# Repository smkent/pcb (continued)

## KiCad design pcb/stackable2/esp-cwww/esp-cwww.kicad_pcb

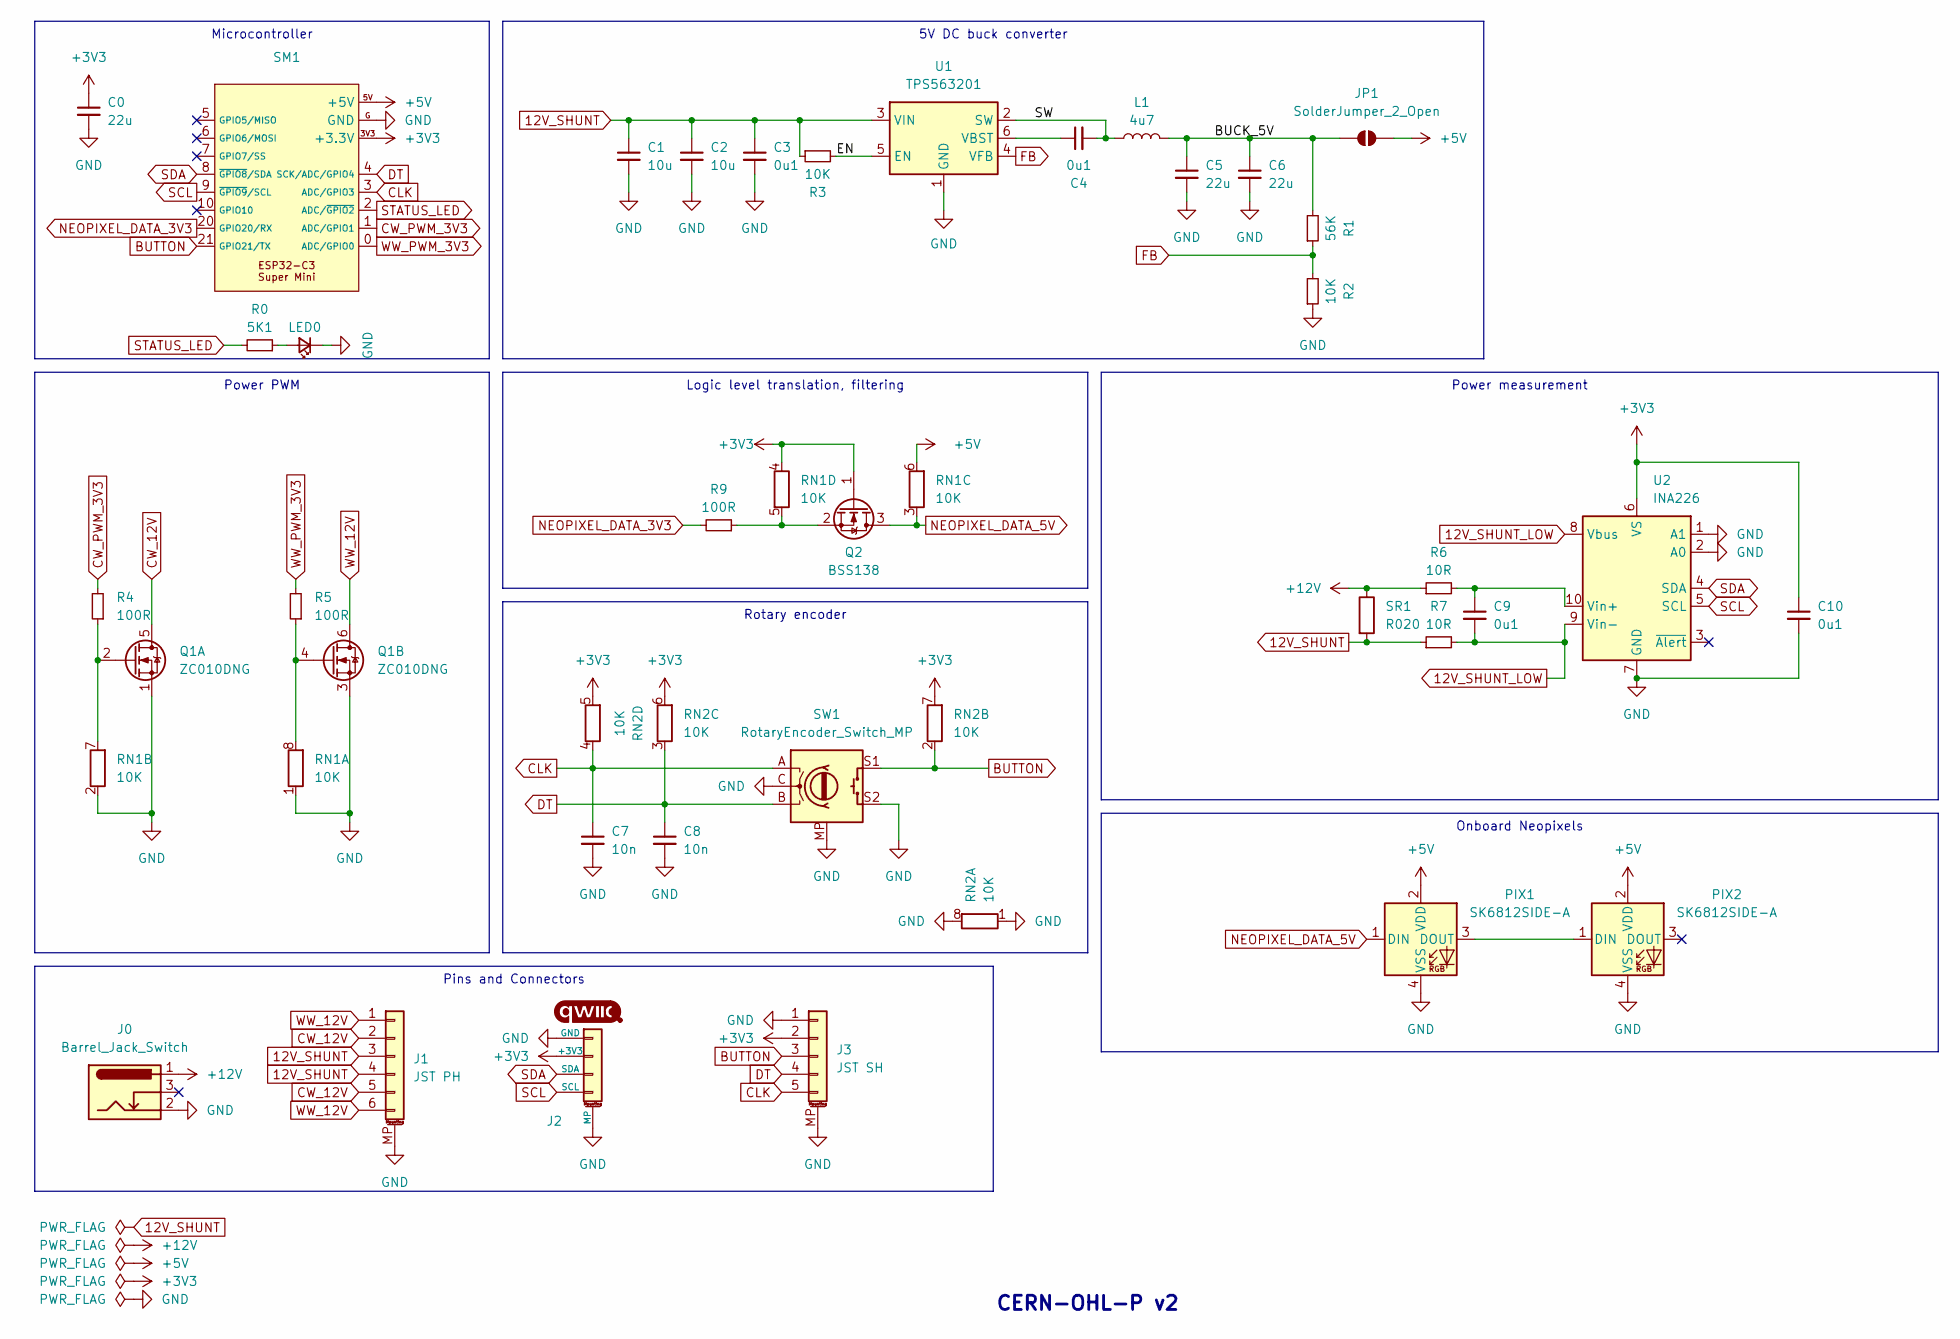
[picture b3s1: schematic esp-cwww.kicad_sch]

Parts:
C0, C5, C6: 22u; C_0603_1608Metric_Pad1.08x0.95mm_HandSolder
C1, C2: 10u; C_0603_1608Metric_Pad1.08x0.95mm_HandSolder
C3, C4: 0u1; C_0603_1608Metric_Pad1.08x0.95mm_HandSolder
C7, C8: 10n; C_0603_1608Metric_Pad1.08x0.95mm_HandSolder
C9, C10: 0u1; C_0402_1005Metric; LCSC Part C152814
J0: Barrel_Jack_Switch; BarrelJack_DC-050_SMT_Horizontal
J1: JST PH; JST_PH_S6B-PH-SM4-TB_1x06-1MP_P2.00mm_Horizontal
J2: Qwiic; Qwiic-SMD-horizontal-logo
J3: JST SH; JST_SH_SM05B-SRSS-TB_1x05-1MP_P1.00mm_Horizontal
JP1: SolderJumper_2_Open; SolderJumper-2_P1.3mm_Open_TrianglePad1.0x1.5mm
L1: 4u7; L_1008_2520Metric
LED0: LED_Small; LED_0603_1608Metric_Pad1.05x0.95mm_HandSolder_simple
PIX1, PIX2: SK6812SIDE-A; LED_SK6812SIDE-A_4.0x1.6mm; LCSC Part C2890037
Q1: ZC010DNG; PDFN-8_L3.2-W3.1-P0.65-LS3.4-BL-EP2; LCSC Part C36499170
Q2: BSS138; SOT-23
R0: 5K1; R_0402_1005Metric
R1: 56K; R_0603_1608Metric_Pad0.98x0.95mm_HandSolder
R2, R3: 10K; R_0603_1608Metric_Pad0.98x0.95mm_HandSolder
R4, R5, R9: 100R; R_0603_1608Metric_Pad0.98x0.95mm_HandSolder
R6, R7: 10R; R_0402_1005Metric; LCSC Part C25077
RN1, RN2: 10K; R_Array_Convex_4x0603
SM1: ESP32-C3-Super-Mini-Castellated-SMD-only
SR1: R020; R_2512_6332Metric_Pad1.40x3.35mm_HandSolder; LCSC Part C5375467
SW1: RotaryEncoder_Switch_MP; RotaryEncoder_Alps_EC11-Switch_Combo_H20mm
U1: TPS563201; SOT-23-6
U2: INA226; VSSOP-10_3x3mm_P0.5mm

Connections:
12V_SHUNT: C1.1, C2.1, C3.1, J1.3, J1.4, R3.1, R7.1, SR1.2, U1.3 (VIN)
12V_SHUNT_LOW: C9.2, R7.2, U2.8 (Vbus), U2.9 (Vin-)
+3V3: C0.1, C10.1, J2.2 (+3V3), J3.2, Q2.1 (G), RN1.4 (R4.1), RN2.5 (R4.2), RN2.6 (R3.2), RN2.7 (R2.2), SM1.3V3 (+3.3V), U2.6 (VS)
+5V: JP1.2 (B), PIX1.2 (VDD), PIX2.2 (VDD), RN1.6 (R3.2), SM1.5V (+5V)
+12V: J0.1, R6.1, SR1.1
/BUCK_5V: C5.1, C6.1, JP1.1 (A), L1.2, R1.2
/EN: R3.2, U1.5 (EN)
/SW: C4.2, L1.1, U1.2 (SW)
BUTTON: J3.3, RN2.2 (R2.1), SM1.21 (GPIO21/TX), SW1.S1
CLK: C7.1, J3.5, RN2.4 (R4.1), SM1.3 (ADC/GPIO3), SW1.A
CW_12V: J1.2, J1.5, Q1.5 (D)
CW_PWM_3V3: R4.2, SM1.1 (ADC/GPIO1)
DT: C8.1, J3.4, RN2.3 (R3.1), SM1.4 (SCK/ADC/GPIO4), SW1.B
FB: R1.1, R2.2, U1.4 (VFB)
GND: C0.2, C1.2, C2.2, C3.2, C5.2, C6.2, C7.2, C8.2, C10.2, J0.2, J1.MP (MountPin), J2.1 (GND), J2.MP, J3.1, J3.MP (MountPin), LED0.1 (K), PIX1.4 (VSS), PIX2.4 (VSS), Q1.1 (S), Q1.3 (S), R2.1, RN1.1 (R1.1), RN1.2 (R2.1), RN2.1 (R1.1), RN2.8 (R1.2), SM1.G (GND), SW1.C, SW1.MP, SW1.S2, U1.1 (GND), U2.1 (A1), U2.2 (A0), U2.7 (GND)
NEOPIXEL_DATA_3V3: R9.2, SM1.20 (GPIO20/RX)
NEOPIXEL_DATA_5V: PIX1.1 (DIN), Q2.3 (D), RN1.3 (R3.1)
unnamed: LED0.2 (A), R0.1
unnamed: PIX1.3 (DOUT), PIX2.1 (DIN)
unnamed: Q1.2 (G), R4.1, RN1.7 (R2.2)
unnamed: Q1.4 (G), R5.1, RN1.8 (R1.2)
unnamed: Q2.2 (S), R9.1, RN1.5 (R4.2)
unnamed: C4.1, U1.6 (VBST)
unnamed: C9.1, R6.2, U2.10 (Vin+)
SCL: J2.4 (SCL), SM1.9 (~GPIO9/SCL), U2.5 (SCL)
SDA: J2.3 (SDA), SM1.8 (~GPIO8/SDA), U2.4 (SDA)
STATUS_LED: R0.2, SM1.2 (ADC/~GPIO2)
WW_12V: J1.1, J1.6, Q1.6 (D)
WW_PWM_3V3: R5.2, SM1.0 (ADC/GPIO0)

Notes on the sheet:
Rotary encoder
5V DC buck converter
Onboard Neopixels
Logic level translation, filtering
Power PWM
Power measurement
Pins and Connectors
Microcontroller
CERN-OHL-P v2

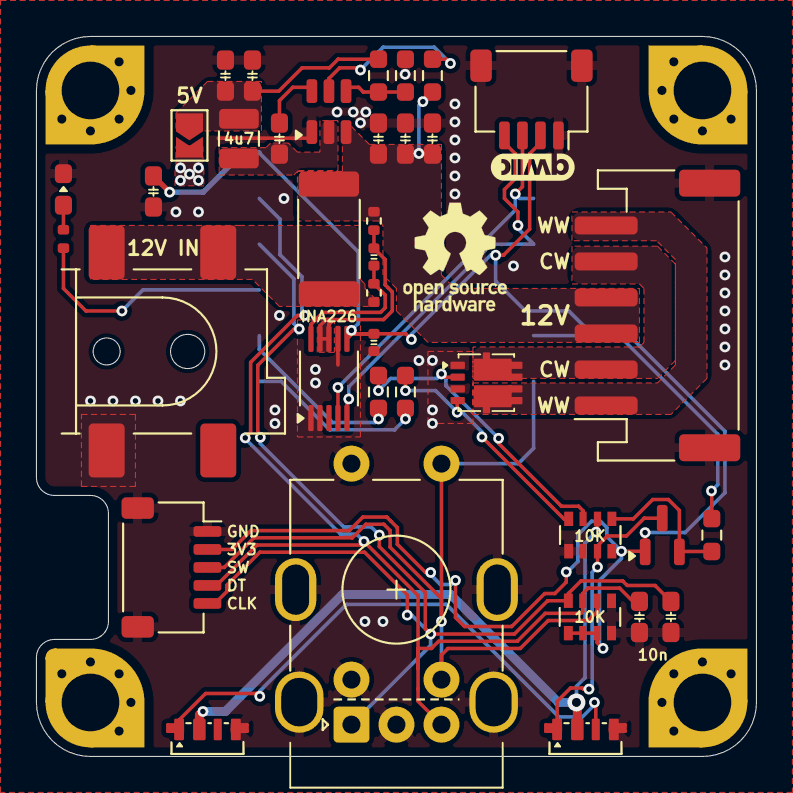
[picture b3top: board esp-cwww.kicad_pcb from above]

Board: 2 copper layers, 40.0 x 40.0 mm, 38 parts (1 on the bottom side), 29 nets.

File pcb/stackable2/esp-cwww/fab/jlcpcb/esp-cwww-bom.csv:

Comment,Designator,Footprint,LCSC
10n,"C7,C8",custom:C_0603_1608Metric_Pad1.08x0.95mm_HandSolder,
INA226,U2,Package_SO:VSSOP-10_3x3mm_P0.5mm,
22u,"C0,C5,C6",custom:C_0603_1608Metric_Pad1.08x0.95mm_HandSolder,
0u1,"C3,C4",custom:C_0603_1608Metric_Pad1.08x0.95mm_HandSolder,
10K,"RN1,RN2",Resistor_SMD:R_Array_Convex_4x0603,
100R,"R4,R5,R9",Resistor_SMD:R_0603_1608Metric_Pad0.98x0.95mm_HandSolder,
LED_Small,LED0,custom:LED_0603_1608Metric_Pad1.05x0.95mm_HandSolder_simple,
Barrel_Jack_Switch,J0,custom:DC-IN_DC-050-2.0-BB_rev2,
Qwiic,J2,connectors:Qwiic-SMD-horizontal-logo,
10u,"C1,C2",custom:C_0603_1608Metric_Pad1.08x0.95mm_HandSolder,
10R,"R6,R7",Resistor_SMD:R_0402_1005Metric,C25077
TPS563201,U1,packages:SOT-23-6,
10K,"R2,R3",Resistor_SMD:R_0603_1608Metric_Pad0.98x0.95mm_HandSolder,
~,SM1,modules:ESP32-C3-Super-Mini-Castellated-SMD-only,
56K,R1,Resistor_SMD:R_0603_1608Metric_Pad0.98x0.95mm_HandSolder,
5K1,R0,passives:R_0402_1005Metric,
0u1,"C9,C10",passives:C_0402_1005Metric,C152814
SK6812SIDE-A,"PIX1,PIX2",lcsc:LED-SK6812SIDE-A-4x1.6mm,
RotaryEncoder_Switch_MP,SW1,custom:RotaryEncoder_Alps_EC11-Switch_Combo_H20mm,
ZC010DNG,Q1,packages:PDFN-8_L3.2-W3.1-P0.65-LS3.4-BL-EP2,C36499170
JST PH,J1,connectors:JST_PH_S6B-PH-SM4-TB_1x06-1MP_P2.00mm_Horizontal,
R020,SR1,Resistor_SMD:R_2512_6332Metric_Pad1.40x3.35mm_HandSolder,C5375467
JST SH,J3,connectors:JST_SH_SM05B-SRSS-TB_1x05-1MP_P1.00mm_Horizontal,
4u7,L1,passives:L_1008_2520Metric,
BSS138,Q2,packages:SOT-23,

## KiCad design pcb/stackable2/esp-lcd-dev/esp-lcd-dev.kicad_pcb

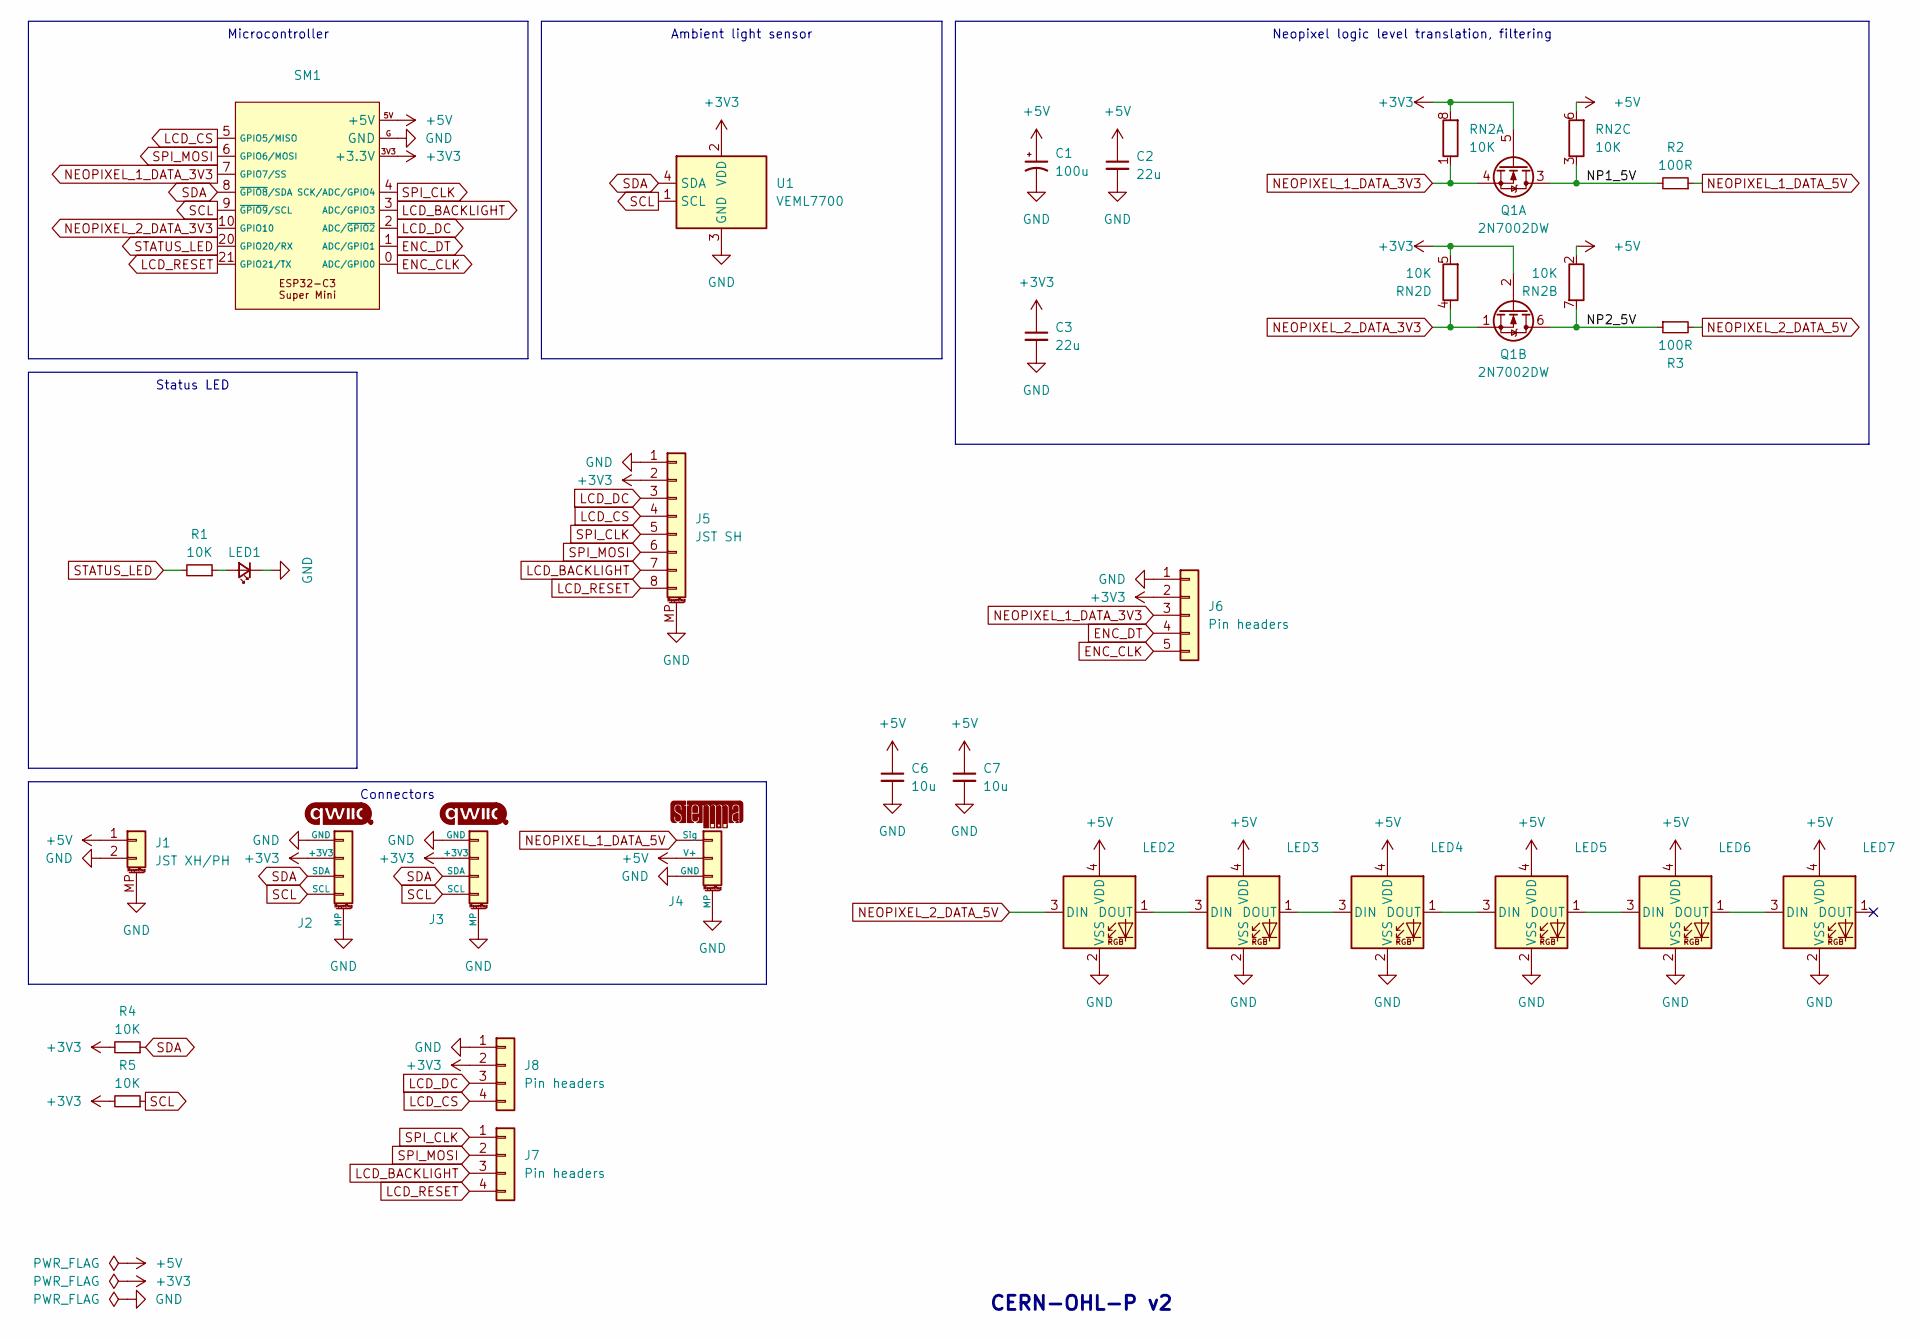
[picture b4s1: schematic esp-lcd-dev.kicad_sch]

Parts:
C1: 100u; CP_Elec_5x5.4
C2, C3: 22u; C_0603_1608Metric_Pad1.08x0.95mm_HandSolder
C6, C7: 10u; C_0603_1608Metric_Pad1.08x0.95mm_HandSolder
J1: JST XH/PH; Conn_Combo_JST-1x02-XH_PH-SMD-pad2gnd
J2, J3: Qwiic; Qwiic-SMD-horizontal-logo-bottom-pinout
J4: STEMMA-Signal; STEMMA-Signal-SMD-horizontal
J5: JST SH; JST_SH_SM08B-SRSS-TB_1x08-1MP_P1.00mm_Horizontal
J6: Pin headers; PinHeader_1x05_P2.54mm_Vertical_simple_pad1gnd
J7: Pin headers; PinSocket_1x04_P2.54mm_Vertical_SMD_Pin1Right
J8: Pin headers; PinSocket_1x04_P2.54mm_Vertical_SMD_Pin1Left
LED1: LED_Small; LED_0603_1608Metric_Pad1.05x0.95mm_HandSolder_simple
LED2, LED3, LED4, LED5, LED6, LED7: WS2812B-2020; LED_WS2812B-2020_PLCC4_2.0x2.0mm_HandSolder
Q1: 2N7002DW; SOT-363_SC-70-6; LCSC Part C5190214
R1, R4, R5: 10K; R_0603_1608Metric_Pad0.98x0.95mm_HandSolder
R2, R3: 100R; R_0603_1608Metric_Pad0.98x0.95mm_HandSolder
RN2: 10K; R_Array_Convex_4x0603
SM1: ESP32-C3-Super-Mini-Castellated-SMD-only
U1: VEML7700; Sensor_VEML7700-TR; LCSC Part C504893

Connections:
+3V3: C3.1, J2.2 (+3V3), J3.2 (+3V3), J5.2, J6.2, J8.2, Q1.2 (G), Q1.5 (G), R4.2, R5.2, RN2.5 (R4.2), RN2.8 (R1.2), SM1.3V3 (+3.3V), U1.2 (VDD)
+5V: C1.1, C2.1, C6.1, C7.1, J1.1, J4.2 (V+), LED2.4 (VDD), LED3.4 (VDD), LED4.4 (VDD), LED5.4 (VDD), LED6.4 (VDD), LED7.4 (VDD), RN2.2 (R2.1), RN2.6 (R3.2), SM1.5V (+5V)
/NP1_5V: Q1.3 (D), R2.2, RN2.3 (R3.1)
/NP2_5V: Q1.6 (D), R3.1, RN2.7 (R2.2)
ENC_CLK: J6.5, SM1.0 (ADC/GPIO0)
ENC_DT: J6.4, SM1.1 (ADC/GPIO1)
GND: C1.2, C2.2, C3.2, C6.2, C7.2, J1.2, J1.MP (MountPin), J2.1 (GND), J2.MP, J3.1 (GND), J3.MP, J4.3 (GND), J4.MP, J5.1, J5.MP (MountPin), J6.1, J8.1, LED1.1 (K), LED2.2 (VSS), LED3.2 (VSS), LED4.2 (VSS), LED5.2 (VSS), LED6.2 (VSS), LED7.2 (VSS), SM1.G (GND), U1.3 (GND)
LCD_BACKLIGHT: J5.7, J7.3, SM1.3 (ADC/GPIO3)
LCD_CS: J5.4, J8.4, SM1.5 (GPIO5/MISO)
LCD_DC: J5.3, J8.3, SM1.2 (ADC/~GPIO2)
LCD_RESET: J5.8, J7.4, SM1.21 (GPIO21/TX)
NEOPIXEL_1_DATA_3V3: J6.3, Q1.4 (S), RN2.1 (R1.1), SM1.7 (GPIO7/SS)
NEOPIXEL_1_DATA_5V: J4.1 (Sig), R2.1
NEOPIXEL_2_DATA_3V3: Q1.1 (S), RN2.4 (R4.1), SM1.10 (GPIO10)
NEOPIXEL_2_DATA_5V: LED2.3 (DIN), R3.2
unnamed: LED1.2 (A), R1.1
unnamed: LED2.1 (DOUT), LED3.3 (DIN)
unnamed: LED3.1 (DOUT), LED4.3 (DIN)
unnamed: LED4.1 (DOUT), LED5.3 (DIN)
unnamed: LED5.1 (DOUT), LED6.3 (DIN)
unnamed: LED6.1 (DOUT), LED7.3 (DIN)
SCL: J2.4 (SCL), J3.4 (SCL), R5.1, SM1.9 (~GPIO9/SCL), U1.1 (SCL)
SDA: J2.3 (SDA), J3.3 (SDA), R4.1, SM1.8 (~GPIO8/SDA), U1.4 (SDA)
SPI_CLK: J5.5, J7.1, SM1.4 (SCK/ADC/GPIO4)
SPI_MOSI: J5.6, J7.2, SM1.6 (GPIO6/MOSI)
STATUS_LED: R1.2, SM1.20 (GPIO20/RX)

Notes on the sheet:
Neopixel logic level translation, filtering
Connectors
Status LED
Ambient light sensor
Microcontroller
CERN-OHL-P v2

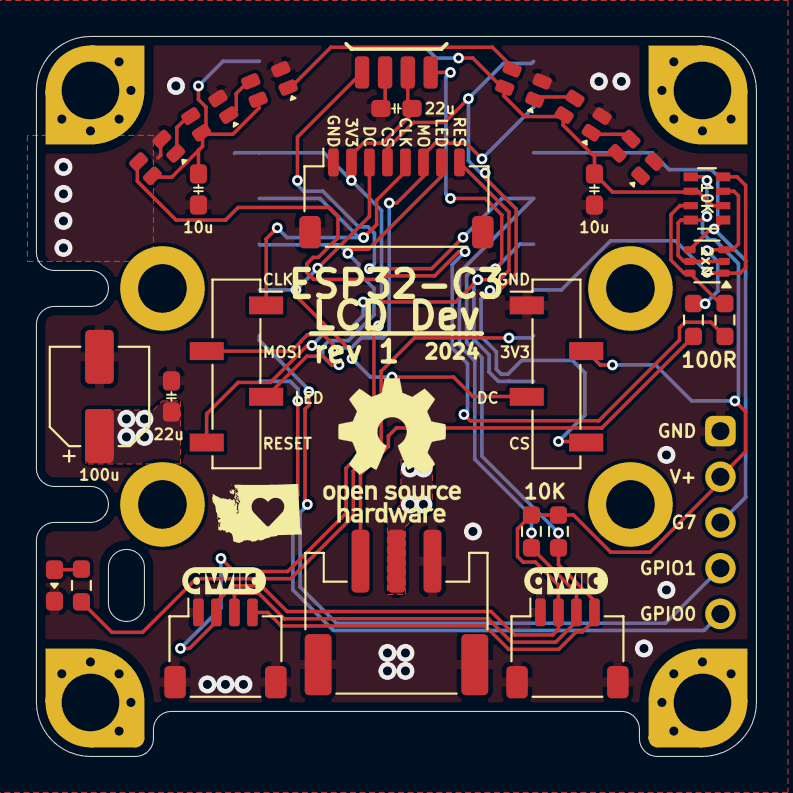
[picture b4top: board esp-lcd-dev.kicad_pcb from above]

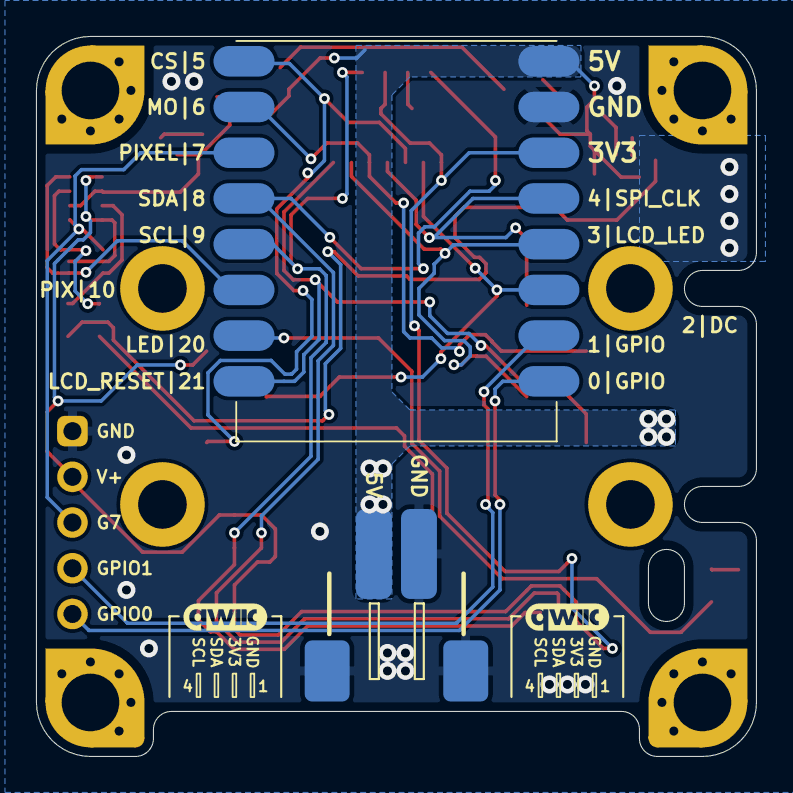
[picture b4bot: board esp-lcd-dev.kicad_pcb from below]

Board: 2 copper layers, 40.0 x 40.0 mm, 29 parts (3 on the bottom side), 26 nets.

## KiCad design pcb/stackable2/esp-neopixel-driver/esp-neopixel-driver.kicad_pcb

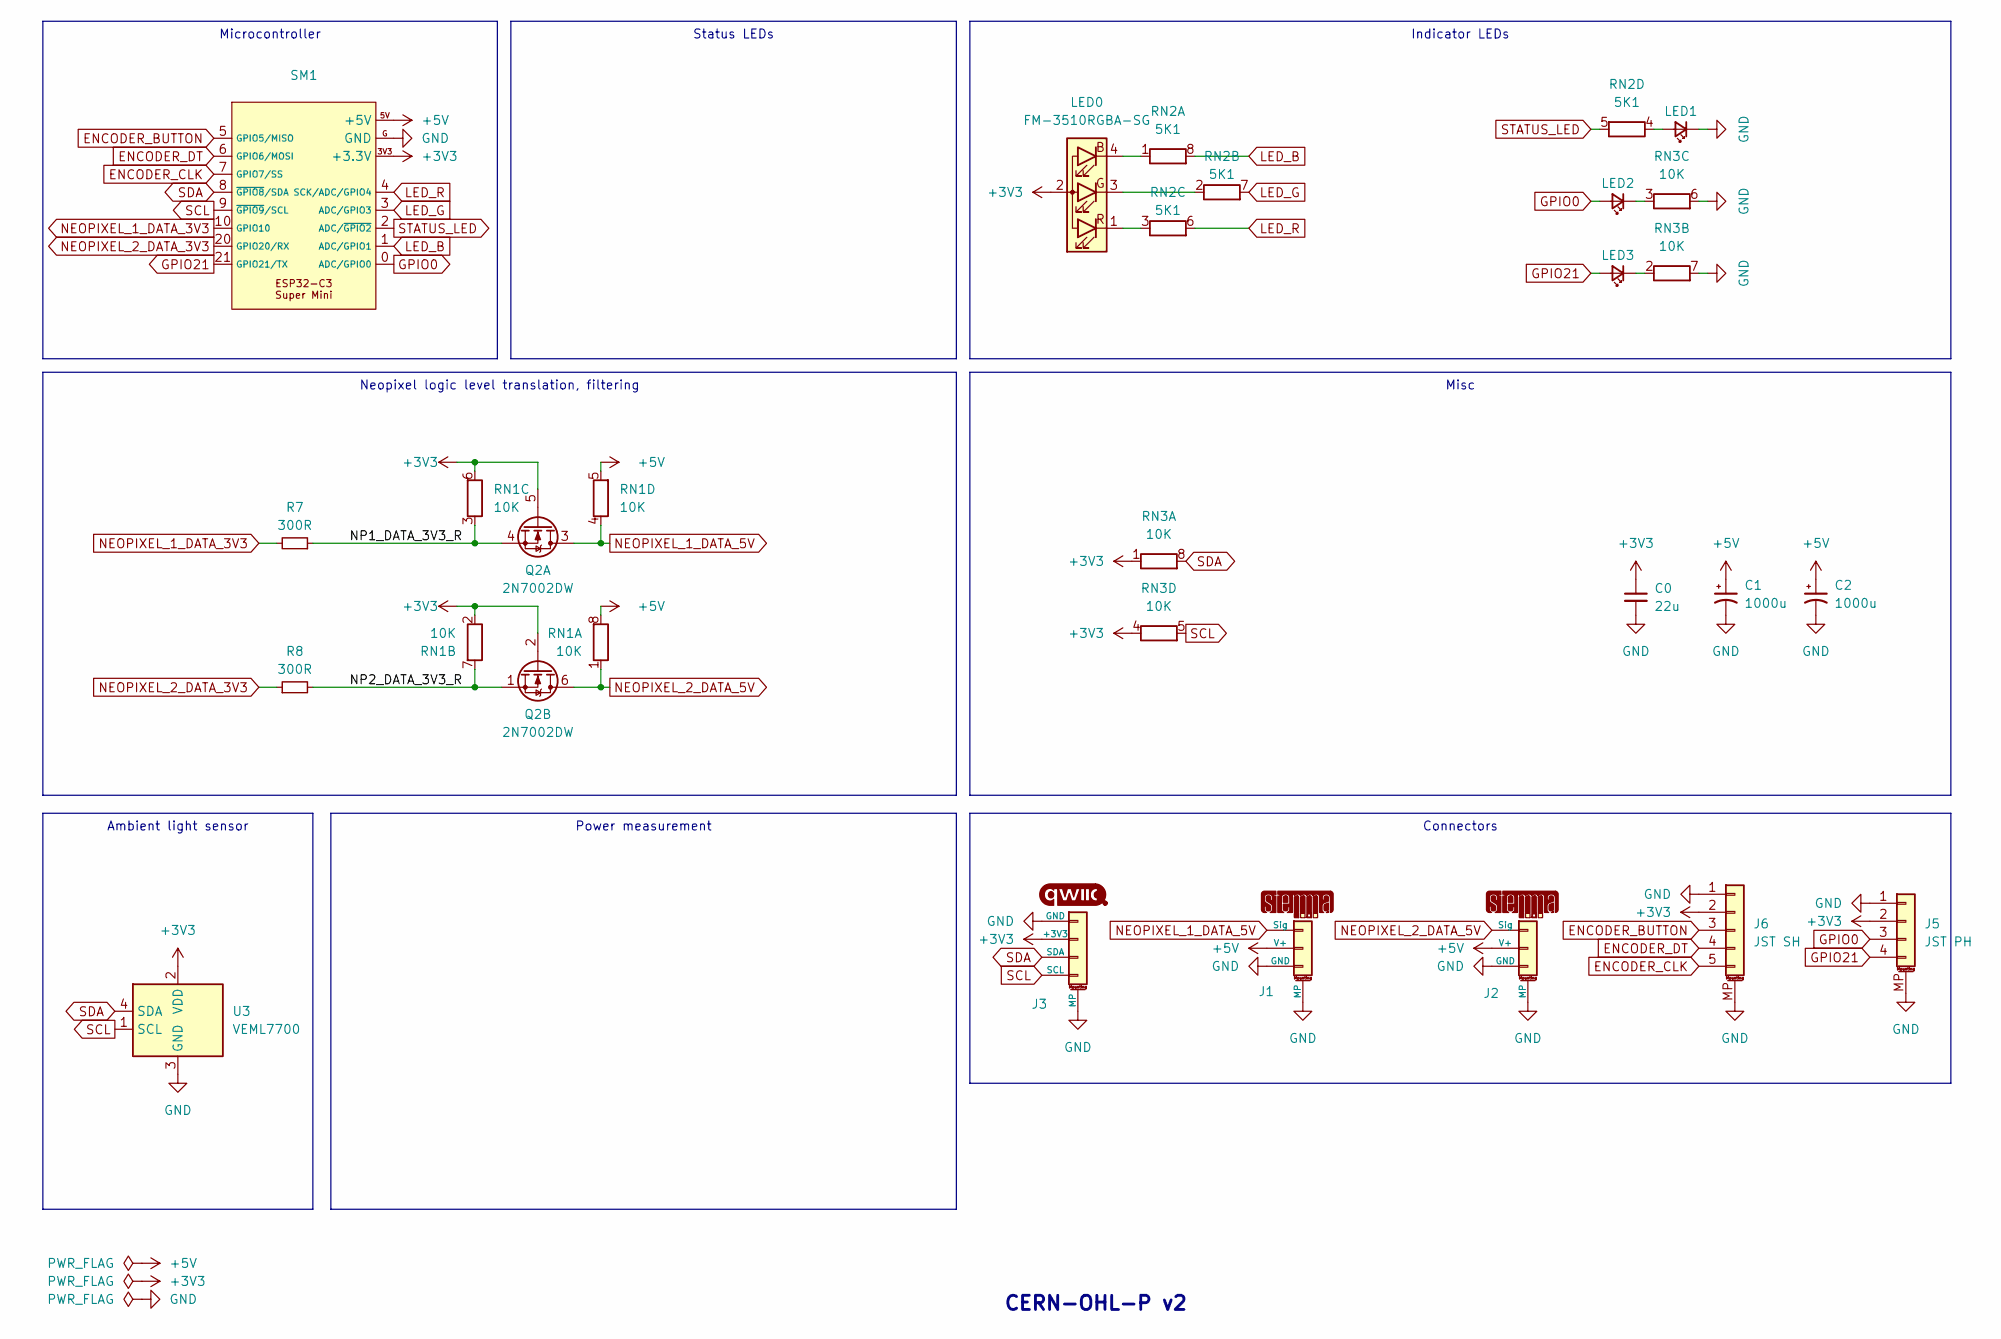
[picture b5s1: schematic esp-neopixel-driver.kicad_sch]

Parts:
C0: 22u; C_0603_1608Metric
C1, C2: 1000u; CP_Elec_8x10
J1, J2: STEMMA-Signal; STEMMA-Signal-SMD-horizontal
J3: Qwiic; Qwiic-SMD-horizontal-logo
J5: JST PH; JST_PH_S4B-PH-SM4-TB_1x04-1MP_P2.00mm_Horizontal
J6: JST SH; JST_SH_SM05B-SRSS-TB_1x05-1MP_P1.00mm_Horizontal
LED0: FM-3510RGBA-SG; LED_RGB_FM-3510RGBA-SG_3.5x1.3mm; LCSC Part C727903
LED1, LED2, LED3: LED_Small; LED_0603_1608Metric
Q2: 2N7002DW; SOT-363_SC-70-6_HandSolder; LCSC Part C5190214
R7, R8: 300R; R_0603_1608Metric
RN1, RN3: 10K; R_Array_Convex_4x0603_HandSolder
RN2: 5K1; R_Array_Convex_4x0603_HandSolder
SM1: ESP32-C3-Super-Mini-Castellated-SMD-only
U3: VEML7700; Sensor_VEML7700-TR; LCSC Part C504893

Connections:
+3V3: C0.1, J3.2 (+3V3), J5.2, J6.2, LED0.2 (A), Q2.2 (G), Q2.5 (G), RN1.2 (R2.1), RN1.6 (R3.2), RN3.1 (R1.1), RN3.4 (R4.1), SM1.3V3 (+3.3V), U3.2 (VDD)
+5V: C1.1, C2.1, J1.2 (V+), J2.2 (V+), RN1.5 (R4.2), RN1.8 (R1.2), SM1.5V (+5V)
/NP1_DATA_3V3_R: Q2.4 (S), R7.1, RN1.3 (R3.1)
/NP2_DATA_3V3_R: Q2.1 (S), R8.2, RN1.7 (R2.2)
ENCODER_BUTTON: J6.3, SM1.5 (GPIO5/MISO)
ENCODER_CLK: J6.5, SM1.7 (GPIO7/SS)
ENCODER_DT: J6.4, SM1.6 (GPIO6/MOSI)
GND: C0.2, C1.2, C2.2, J1.3 (GND), J1.MP, J2.3 (GND), J2.MP, J3.1 (GND), J3.MP, J5.1, J5.MP (MountPin), J6.1, J6.MP (MountPin), LED1.1 (K), RN3.6 (R3.2), RN3.7 (R2.2), SM1.G (GND), U3.3 (GND)
GPIO0: J5.3, LED2.2 (A), SM1.0 (ADC/GPIO0)
GPIO21: J5.4, LED3.2 (A), SM1.21 (GPIO21/TX)
LED_B: RN2.8 (R1.2), SM1.1 (ADC/GPIO1)
LED_G: RN2.7 (R2.2), SM1.3 (ADC/GPIO3)
LED_R: RN2.6 (R3.2), SM1.4 (SCK/ADC/GPIO4)
NEOPIXEL_1_DATA_3V3: R7.2, SM1.10 (GPIO10)
NEOPIXEL_1_DATA_5V: J1.1 (Sig), Q2.3 (D), RN1.4 (R4.1)
NEOPIXEL_2_DATA_3V3: R8.1, SM1.20 (GPIO20/RX)
NEOPIXEL_2_DATA_5V: J2.1 (Sig), Q2.6 (D), RN1.1 (R1.1)
unnamed: LED0.4 (BK), RN2.1 (R1.1)
unnamed: LED0.3 (GK), RN2.2 (R2.1)
unnamed: LED0.1 (RK), RN2.3 (R3.1)
unnamed: LED1.2 (A), RN2.4 (R4.1)
unnamed: LED2.1 (K), RN3.3 (R3.1)
unnamed: LED3.1 (K), RN3.2 (R2.1)
SCL: J3.4 (SCL), RN3.5 (R4.2), SM1.9 (~GPIO9/SCL), U3.1 (SCL)
SDA: J3.3 (SDA), RN3.8 (R1.2), SM1.8 (~GPIO8/SDA), U3.4 (SDA)
STATUS_LED: RN2.5 (R4.2), SM1.2 (ADC/~GPIO2)

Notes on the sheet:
Status LEDs
Indicator LEDs
Microcontroller
Misc
Ambient light sensor
Connectors
Power measurement
Neopixel logic level translation, filtering
CERN-OHL-P v2

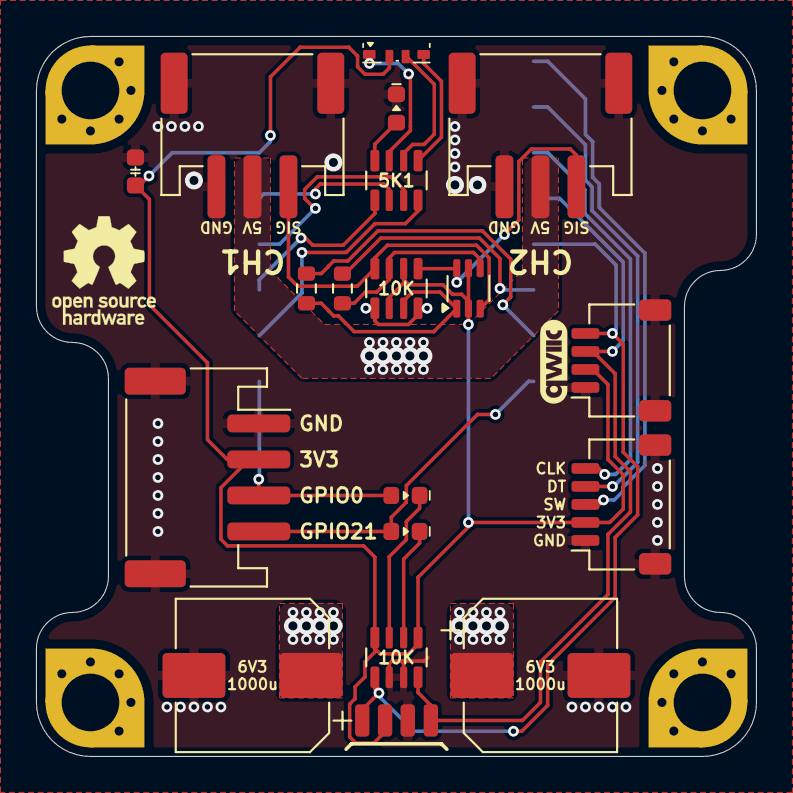
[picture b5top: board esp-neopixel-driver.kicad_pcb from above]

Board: 2 copper layers, 40.0 x 40.0 mm, 24 parts (1 on the bottom side), 26 nets.

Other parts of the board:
MH_NE: MountingHole_3.2mm_M3_Pad_Via_corner_compact
MH_NW: MountingHole_3.2mm_M3_Pad_Via_corner_compact
MH_SE: MountingHole_3.2mm_M3_Pad_Via_corner_compact
MH_SW: MountingHole_3.2mm_M3_Pad_Via_corner_compact

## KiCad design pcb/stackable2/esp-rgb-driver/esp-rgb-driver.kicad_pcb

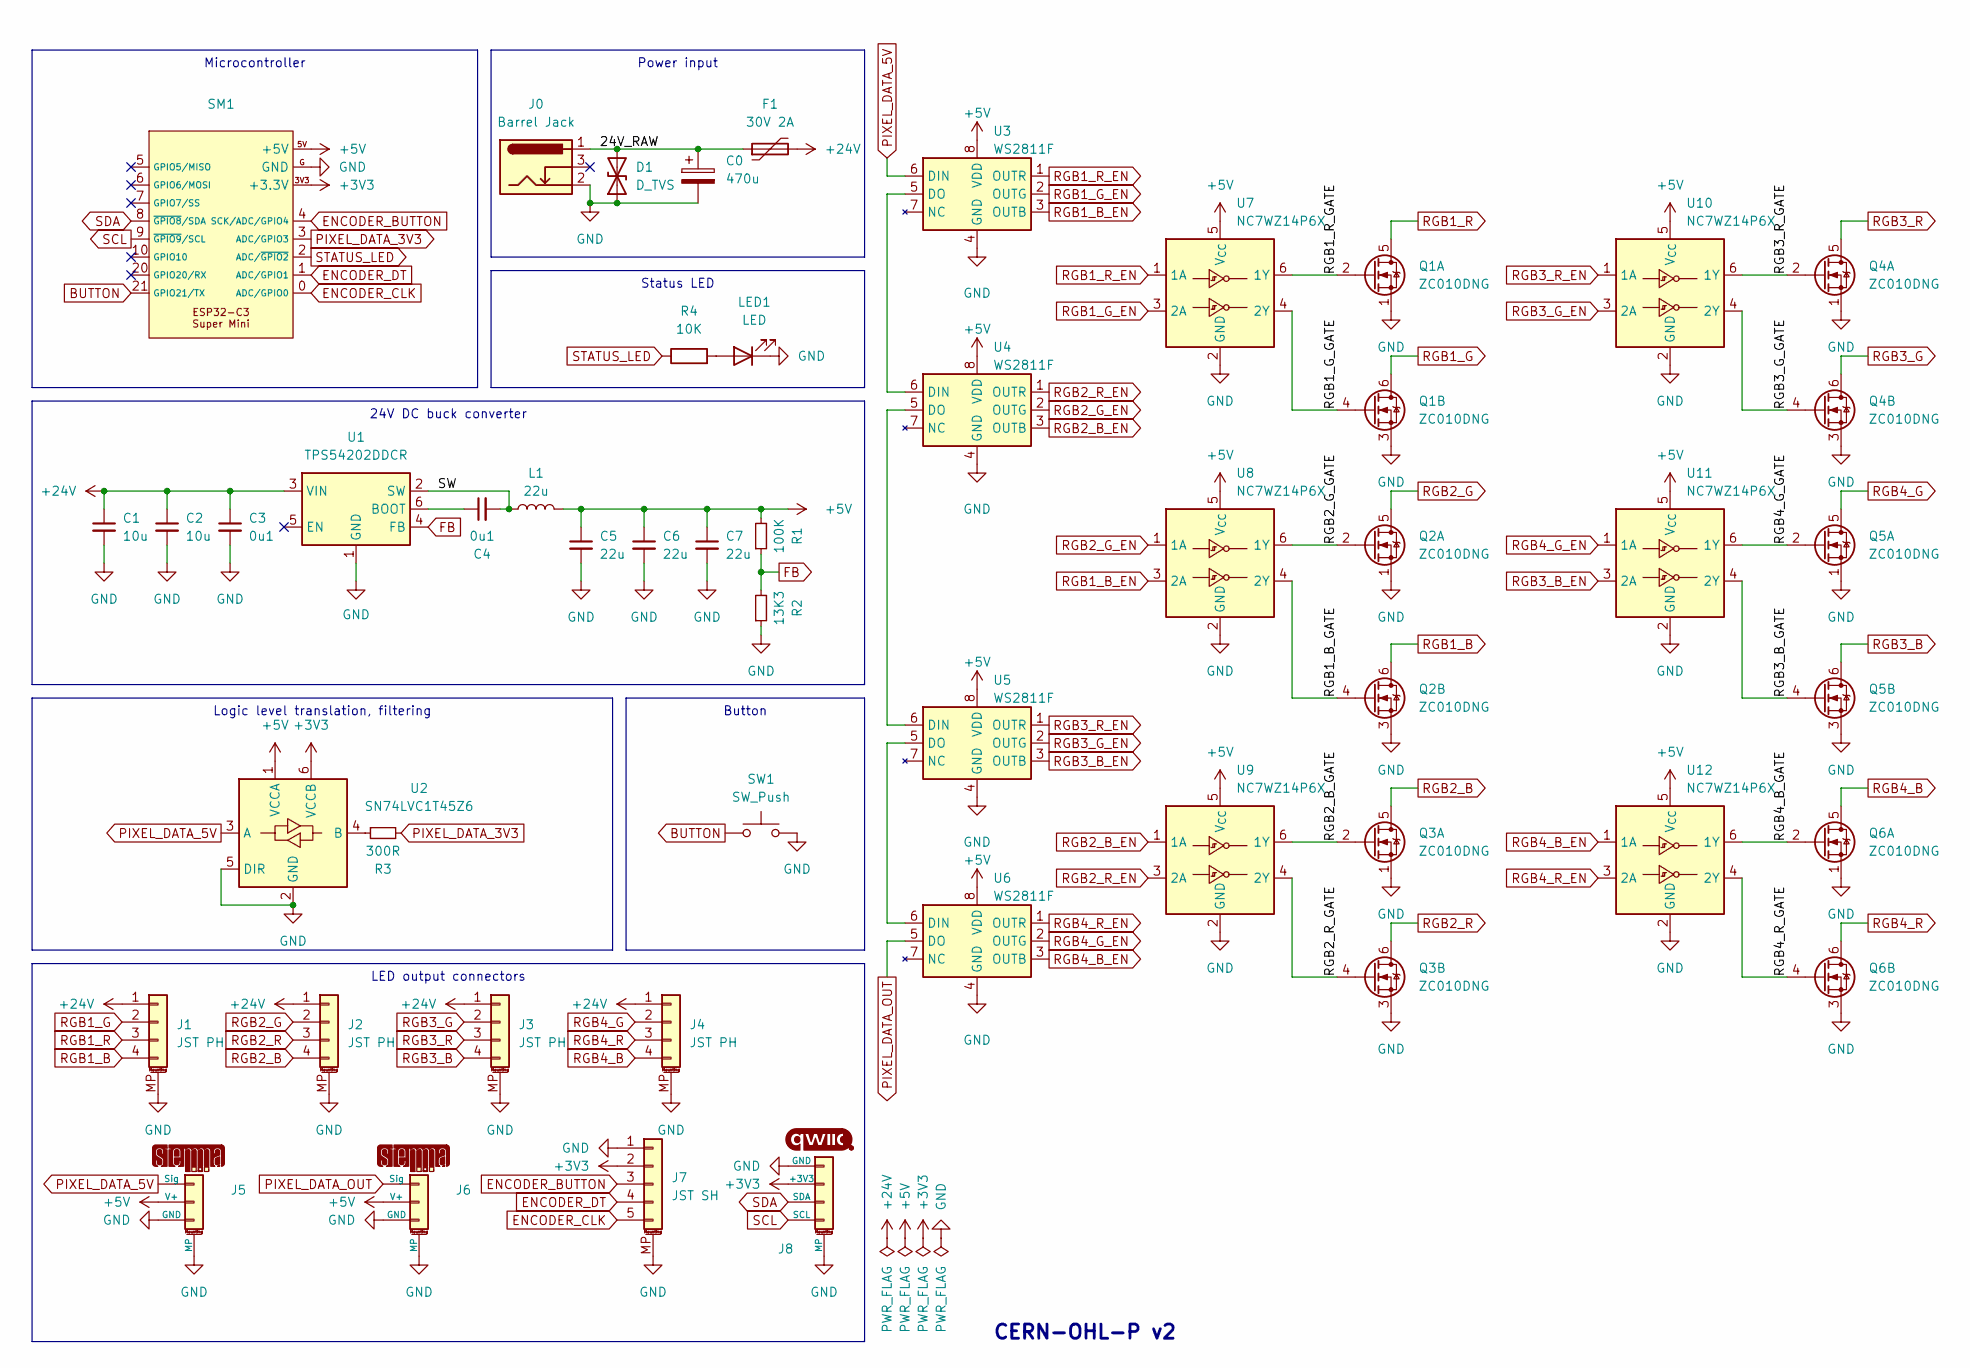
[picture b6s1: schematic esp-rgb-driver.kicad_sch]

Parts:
C0: 470u; CP_Elec_8x10
C1, C2: 10u; C_0603_1608Metric_Pad1.08x0.95mm_HandSolder
C3, C4: 0u1; C_0402_1005Metric
C5, C6, C7: 22u; C_0805_2012Metric_Pad1.18x1.45mm_HandSolder
D1: D_TVS; D_SOD-123F
F1: 30V 2A; Fuse_1812_4532Metric
J0: Barrel Jack; BarrelJack_DC-050_SMT_Horizontal
J1, J2, J3, J4: JST PH; JST_PH_S4B-PH-SM4-TB_1x04-1MP_P2.00mm_Horizontal
J5, J6: STEMMA-Signal; STEMMA-Signal-SMD-horizontal
J7: JST SH; JST_SH_SM05B-SRSS-TB_1x05-1MP_P1.00mm_Horizontal
J8: Qwiic; Qwiic-SMD-horizontal-logo
L1: 22u; L_Power_7.0x6.6mm_0630
LED1: LED; LED_0402_1005Metric
Q1, Q2, Q3, Q4, Q5, Q6: ZC010DNG; PDFN-8_L3.2-W3.1-P0.65-LS3.4-BL-EP2; LCSC Part C36499170
R1: 100K; R_0603_1608Metric_Pad0.98x0.95mm_HandSolder
R2: 13K3; R_0603_1608Metric_Pad0.98x0.95mm_HandSolder
R3: 300R; R_0402_1005Metric
R4: 10K; R_0402_1005Metric
SM1: ESP32-C3-Super-Mini-Castellated-SMD-only
SW1: SW_Push; SW_SPST_PTS647_Sx50
U1: TPS54202DDCR; SOT-23-6; LCSC Part C191884
U2: SN74LVC1T45Z6; SOT-563; LCSC Part C441819
U3, U4, U5, U6: WS2811F; FSOP-8_3.3x1.7mm_P0.80mm; LCSC Part C5446692
U7, U8, U9, U10, U11, U12: NC7WZ14P6X; SOT-363_SC-70-6_HandSolder; LCSC Part C5207816

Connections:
+3V3: J7.2, J8.2 (+3V3), SM1.3V3 (+3.3V), U2.6 (VCCB)
+5V: C5.1, C6.1, C7.1, J5.2 (V+), J6.2 (V+), L1.2, R1.2, SM1.5V (+5V), U2.1 (VCCA), U3.8 (VDD), U4.8 (VDD), U5.8 (VDD), U6.8 (VDD), U7.5 (V_{CC}), U8.5 (V_{CC}), U9.5 (V_{CC}), U10.5 (V_{CC}), U11.5 (V_{CC}), U12.5 (V_{CC})
+24V: C1.1, C2.1, C3.1, F1.2, J1.1, J2.1, J3.1, J4.1, U1.3 (VIN)
/24V_RAW: C0.1, D1.2 (A2), F1.1, J0.1
/RGB1_B_GATE: Q2.4 (G), U8.4 (2Y)
/RGB1_G_GATE: Q1.4 (G), U7.4 (2Y)
/RGB1_R_GATE: Q1.2 (G), U7.6 (1Y)
/RGB2_B_GATE: Q3.2 (G), U9.6 (1Y)
/RGB2_G_GATE: Q2.2 (G), U8.6 (1Y)
/RGB2_R_GATE: Q3.4 (G), U9.4 (2Y)
/RGB3_B_GATE: Q5.4 (G), U11.4 (2Y)
/RGB3_G_GATE: Q4.4 (G), U10.4 (2Y)
/RGB3_R_GATE: Q4.2 (G), U10.6 (1Y)
/RGB4_B_GATE: Q6.2 (G), U12.6 (1Y)
/RGB4_G_GATE: Q5.2 (G), U11.6 (1Y)
/RGB4_R_GATE: Q6.4 (G), U12.4 (2Y)
/SW: C4.2, L1.1, U1.2 (SW)
BUTTON: SM1.21 (GPIO21/TX), SW1.1
ENCODER_BUTTON: J7.3, SM1.4 (SCK/ADC/GPIO4)
ENCODER_CLK: J7.5, SM1.0 (ADC/GPIO0)
ENCODER_DT: J7.4, SM1.1 (ADC/GPIO1)
FB: R1.1, R2.2, U1.4 (FB)
GND: C0.2, C1.2, C2.2, C3.2, C5.2, C6.2, C7.2, D1.1 (A1), J0.2, J1.MP (MountPin), J2.MP (MountPin), J3.MP (MountPin), J4.MP (MountPin), J5.3 (GND), J5.MP, J6.3 (GND), J6.MP, J7.1, J7.MP (MountPin), J8.1 (GND), J8.MP, LED1.1 (K), Q1.1 (S), Q1.3 (S), Q2.1 (S), Q2.3 (S), Q3.1 (S), Q3.3 (S), Q4.1 (S), Q4.3 (S), Q5.1 (S), Q5.3 (S), Q6.1 (S), Q6.3 (S), R2.1, SM1.G (GND), SW1.2, U1.1 (GND), U2.2 (GND), U2.5 (DIR), U3.4 (GND), U4.4 (GND), U5.4 (GND), U6.4 (GND), U7.2 (GND), U8.2 (GND), U9.2 (GND), U10.2 (GND), U11.2 (GND), U12.2 (GND)
unnamed: LED1.2 (A), R4.2
unnamed: C4.1, U1.6 (BOOT)
unnamed: R3.1, U2.4 (B)
unnamed: U3.5 (DO), U4.6 (DIN)
unnamed: U4.5 (DO), U5.6 (DIN)
unnamed: U5.5 (DO), U6.6 (DIN)
PIXEL_DATA_3V3: R3.2, SM1.3 (ADC/GPIO3)
PIXEL_DATA_5V: J5.1 (Sig), U2.3 (A), U3.6 (DIN)
PIXEL_DATA_OUT: J6.1 (Sig), U6.5 (DO)
RGB1_B: J1.4, Q2.6 (D)
RGB1_B_EN: U3.3 (OUTB), U8.3 (2A)
RGB1_G: J1.2, Q1.6 (D)
RGB1_G_EN: U3.2 (OUTG), U7.3 (2A)
RGB1_R: J1.3, Q1.5 (D)
RGB1_R_EN: U3.1 (OUTR), U7.1 (1A)
RGB2_B: J2.4, Q3.5 (D)
RGB2_B_EN: U4.3 (OUTB), U9.1 (1A)
RGB2_G: J2.2, Q2.5 (D)
RGB2_G_EN: U4.2 (OUTG), U8.1 (1A)
RGB2_R: J2.3, Q3.6 (D)
RGB2_R_EN: U4.1 (OUTR), U9.3 (2A)
RGB3_B: J3.4, Q5.6 (D)
RGB3_B_EN: U5.3 (OUTB), U11.3 (2A)
RGB3_G: J3.2, Q4.6 (D)
RGB3_G_EN: U5.2 (OUTG), U10.3 (2A)
RGB3_R: J3.3, Q4.5 (D)
RGB3_R_EN: U5.1 (OUTR), U10.1 (1A)
RGB4_B: J4.4, Q6.5 (D)
RGB4_B_EN: U6.3 (OUTB), U12.1 (1A)
RGB4_G: J4.2, Q5.5 (D)
RGB4_G_EN: U6.2 (OUTG), U11.1 (1A)
RGB4_R: J4.3, Q6.6 (D)
RGB4_R_EN: U6.1 (OUTR), U12.3 (2A)
SCL: J8.4 (SCL), SM1.9 (~GPIO9/SCL)
SDA: J8.3 (SDA), SM1.8 (~GPIO8/SDA)
STATUS_LED: R4.1, SM1.2 (ADC/~GPIO2)

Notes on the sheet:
24V DC buck converter
Status LED
Button
Microcontroller
Logic level translation, filtering
LED output connectors
Power input
CERN-OHL-P v2
